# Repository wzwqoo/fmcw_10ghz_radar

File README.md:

# 10 GHz FMCW Radar Sensing Platform

A single-board **1TX / 3RX, 10 GHz FMCW radar**, its **Artix-7 range–Doppler–CFAR
backend**, and the **carrier board** that mounts the radar alongside a
global-shutter camera and an impact microphone.

The target application is a golf launch monitor: recover a ball's speed, launch
direction, spin rate and spin axis from one radar and one camera. That
application drives every architectural choice here — three non-collinear
receivers (the minimum that gives a radar-native spin axis), per-receiver
*complex* range–Doppler maps published to DDR3 (the phase the spin-axis
interferometer consumes), and a once-per-shot Ethernet offload so the heavy
post-processing runs on a host PC instead of in fabric.

```
┌─ rf_frontend/ — 10 GHz FMCW front-end ────────────────────────────────────┐
│                                                                           │
│  ADF4159 ramp PLL ──► HMC1163 10 GHz VCO ──► 4 dB branchline coupler      │
│                                                │             │            │
│                                     TX patch column    1→3 Wilkinson tree │
│                                                              │ LO         │
│  RX patch column ×3 ──► PMA3-14LN+ ──► LTC5548 ◄─────────────┘            │
│                                           │                               │
│                           ADA4940-2 IF ───┴──► ADAR7251  4 ch, 16-bit,    │
│                                                          simultaneous     │
│                                                                           │
└───────────────────────────────────────────────────────────────────────────┘
                                        │  40-pin FPC
                                        ▼
┌─ carrier_board/ — camera + radar carrier ─────────────────────────────────┐
│                                                                           │
│  radar 40-pin FPC ────────────────────────┐                               │
│  OV9281 ──MIPI──► TC358748 ──parallel─────┼──► 140-pin B2B ──► FPGA module│
│  INMP441 ──────────I2S────────────────────┘                               │
│                                                                           │
│  RTL8211F 1 GbE ◄─────────────────────────────────────────── UDP offload  │
│                                                                           │
└───────────────────────────────────────────────────────────────────────────┘
                                        │  parallel + I2S over the B2B connector
                                        ▼
┌─ fpga/ — Artix-7 backend ─────────────────────────────────────────────────┐
│                                                                           │
│  PPI bytes ──► TDM ──► BPF + Hilbert FIR ──► range FFT ×3 ──► DDR A       │
│                                                                │          │
│                        Doppler FFT ×3 ◄────────────────────────┘          │
│                              ├──► DDR B   per-RX complex RD maps          │
│                              └──► Σ|X|² ──► DDR C ──► CFAR ──► DDR D      │
│                                                                           │
│  audio + speed trigger ──► one-shot B/C/D dump ──► UDP packetizer         │
│                                                                           │
└───────────────────────────────────────────────────────────────────────────┘
                                        │
                                        ▼  host PC — trajectory, angle of arrival, spin
```

## Repository structure

| Path | Subsystem |
|---|---|
| [`rf_frontend/`](rf_frontend/) | The 10 GHz 1TX/3RX FMCW front-end: KiCad schematics and PCB on Isola 370HR, plus the ADS/Momentum EM results for every distributed structure |
| [`fpga/`](fpga/) | Artix-7 gateware: the raw-ADC → range–Doppler → CFAR pipeline, the DDR-to-host UDP offload path, MicroBlaze firmware, and the simulation stack |
| [`carrier_board/`](carrier_board/) | The carrier PCB that ties camera, radar, FPGA module, Ethernet and audio together, plus the CS-mount lens mechanics |

Each subsystem has its own README with the detail; the tables below are the map.

### `rf_frontend/` — 10 GHz FMCW front-end

A closed-loop fractional-N ramp PLL (ADF4159) drives a 10 GHz VCO (HMC1163)
across a 192 MHz sweep in 108 µs. The VCO fundamental is tapped through a 4 dB
branchline coupler and a 1→3 Wilkinson tree to supply a coherent LO to three
LNA-first receive chains (PMA3-14LN+ → LTC5548 → ADA4940-2), which land on an
ADAR7251's simultaneously-sampled channels. The antennas are series-fed patch
columns arranged in a staggered "^", stepped λ/2 between adjacent phase centres
in both array axes, so per-Doppler-bin angles never wrap.

→ [`rf_frontend/README.md`](rf_frontend/README.md)

### `fpga/` — Artix-7 digital backend

`01_adar7251_ppi_rx` → TDM mux → band-pass + Hilbert FIR → per-RX range FFT →
transposed DDR scatter (region A) → Doppler sequencer → per-RX Doppler FFT →
non-coherent integration (region C) + per-RX complex cache (region B) →
streaming cell-averaging CFAR (region D). A 128 × 256 grid, double-buffered so
software never reads a torn frame. An audio-plus-speed trigger picks the first
frame after impact that clears both gates and dumps its B/C/D regions to the
host over UDP.

→ [`fpga/README.md`](fpga/README.md)

### `carrier_board/` — camera + radar carrier

Hosts the camera FPC, the radar's 40-pin FPC, a 140-pin B2B connector to the
FPGA module, I2S audio headers, gigabit Ethernet and the power tree. Two
revisions live here: the current OV9281 design (schematics complete, layout not
yet drawn) and the earlier IMX477 design, which is where the completed layout
is.

→ [`carrier_board/README.md`](carrier_board/README.md)

## Status

| Item | State |
|---|---|
| `rf_frontend/` schematics + PCB layout | Complete; every distributed structure verified in ADS/Momentum |
| `fpga/` RTL pipeline (`01`…`08`) | Complete; unit tests and a raw-ADC-to-CFAR xsim run against the real Xilinx FFT/FIR IP |
| `fpga/` host offload (streamer, packetizer, receiver) | Complete and unit-tested |
| `fpga/firmware/audio_dsp.c` | Complete |
| `fpga/firmware/fusion_control.c` | **Work in progress** — the audio + speed trigger FSM and its frame-selection policy are still being written |
| `carrier_board/ov9281/` | **Work in progress** — schematics done, PCB layout not yet started |
| `carrier_board/imx477/` | Obsolete and not optimized — rolling-shutter sensor, hand-unfriendly USB 3.0 BGA. Kept as the revision with a finished layout |

## Toolchain

| Tool | Used for |
|---|---|
| KiCad ≥ 8 | `rf_frontend/kicad/`, `carrier_board/ov9281/`, `carrier_board/imx477/` |
| Keysight ADS + Momentum | EM verification of the antenna, coupler, splitter and LO tree |
| Vivado 2025.1 | Block design, IP generation, synthesis, the xsim end-to-end run |
| Icarus Verilog | The RTL unit tests — they need no vendor IP (`fpga/sim/run_unit_tests.sh`) |
| Python 3 (numpy, matplotlib) | Stimulus generation, CFAR golden checks, the UDP frame receiver |
| FreeCAD | `carrier_board/mechanical/CS-mount.FCStd` |

Large generated trees are deliberately out of the repository: the Vivado
project's `.runs`/`.gen`/`.cache` output, xsim build directories, and the ADS
workspace (its results are captured as images in `rf_frontend/ads/`).

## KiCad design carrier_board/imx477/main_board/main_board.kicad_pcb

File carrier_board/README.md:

# `carrier_board/` — camera + radar carrier

The board everything else plugs into: the camera, the radar, the FPGA module,
the impact microphone, Ethernet, and the power tree.

Two revisions live here. **`ov9281/` is the current design and is a work in
progress** — the schematics are complete, the PCB layout is not yet drawn.
`imx477/` is the earlier revision, superseded but kept because it is the one
with a finished layout.

---

## `ov9281/` — current revision (work in progress)

Built around the **OV9281 global-shutter sensor**. Its interfaces:

| Sheet | Interface |
|---|---|
| `extension.kicad_sch` (CAM) | Camera **FPC connector**; the sensor's MIPI CSI-2 lanes into a **TC358748XBG** bridge, which presents them as a parallel bus (PD0–PD23, PCLK, HVALID, VVALID) the FPGA captures directly. PCA9543 I²C switch and TXS0108E level shifters alongside |
| `FPGA.kicad_sch` | **140-pin board-to-board connector** (2×70, 0.5 mm) carrying the parallel camera bus, radar bus and control to the FPGA module; JTAG; and the **I²S audio headers** (BCLK / LRCLK / SD) for the impact microphone |
| `FMCW.kicad_sch` | **40-pin shielded FPC connector** to the radar front-end, with TXS0108E level translation |
| `ETH.kicad_sch` | **Gigabit Ethernet**: RTL8211F-CG PHY, HY911130A RJ45 with integrated magnetics, SN74LVC2G34 buffers |
| `power.kicad_sch` | 12 V barrel jack → TPS54302 buck and TPS74801 LDO rails |
| `footprints/` | Project-local footprint libraries |

**Layout status: not started.** `ov9281/` is schematics only — there is no
`.kicad_pcb` in this revision.

### Why Ethernet and not USB 3.0

The IMX477 revision used a CYUSB3014 for the host link. That part is a
**121-ball TFBGA**, which is not realistically hand-reflowable, and it dictated
the whole main-board stackup and layout. The OV9281 revision drops it for
gigabit Ethernet through an RTL8211F, which is a QFN and reflows by hand
without difficulty.

That change also settled the processing split. Because frames are **buffered in
DDR and then sent to a PC for processing**, rather than being consumed live on
the FPGA, the **on-FPGA blob-detection logic from the IMX477 era is obsolete**.
The FPGA's job is now capture, buffer, and offload; detection, trajectory
fitting and spin estimation all happen on the host. The radar path in
[`../fpga`](../fpga) follows the same store-and-forward pattern.

---

## `imx477/` — earlier revision (obsolete)

Built around the **IMX477**, split across a `main_board/` (FPGA module, USB 3.0
host link, power) and a separate `sensor_board/`, joined by a DF40C/DF40HC
60-pin board-to-board pair.

**The IMX477 is obsolete for this application, and this revision is not
optimized.** The sensor is rolling-shutter, which smears a fast-moving ball
across the frame in a way no amount of downstream processing recovers — a
global-shutter sensor is the requirement, and that is what the OV9281 revision
exists to satisfy. The USB 3.0 host path is the second reason it was dropped
(see above).

It is kept here because it is the only revision that carries a completed PCB
layout, and because its power tree and B2B pinout carry over.

| Path | Contents |
|---|---|
| `imx477/main_board/main_board.kicad_pro` / `.kicad_sch` / `.kicad_pcb` | KiCad project, schematics, and the finished layout |
| `imx477/main_board/USB3.kicad_sch` | CYUSB3014 USB 3.0 controller, AT24CM02 config EEPROM, VBUS switching — the path replaced by Ethernet |
| `imx477/main_board/FPGA.kicad_sch` | 2×70 B2B to the FPGA module, JTAG |
| `imx477/main_board/extension.kicad_sch` | DF40HC 60-pin B2B to the sensor board |
| `imx477/main_board/power.kicad_sch` | TLV62130 / AP3417C / MIC5504 rails |
| `imx477/sensor_board/` | The IMX477 sensor board: `sensors.kicad_sch`, `power.kicad_sch`, and its layout |
| `imx477/footprints/` | Project-local footprint libraries |

---

## `mechanical/`

`CS-mount.FCStd` — a FreeCAD CS-mount lens holder, drawn for the IMX477 sensor
board. `lens_spec.png` records the optics it was sized around: a 4 mm lens
giving roughly 90° horizontal field of view, paired with 940 nm IR flood
illumination so exposures stay short enough for 200 fps and above.

---

## Opening the boards

```
kicad carrier_board/ov9281/hardware.kicad_pro           # KiCad 8 or newer
kicad carrier_board/imx477/main_board/main_board.kicad_pro
kicad carrier_board/imx477/sensor_board/sensor_board.kicad_pro
```

The render above was produced with `kicad-cli pcb render`.

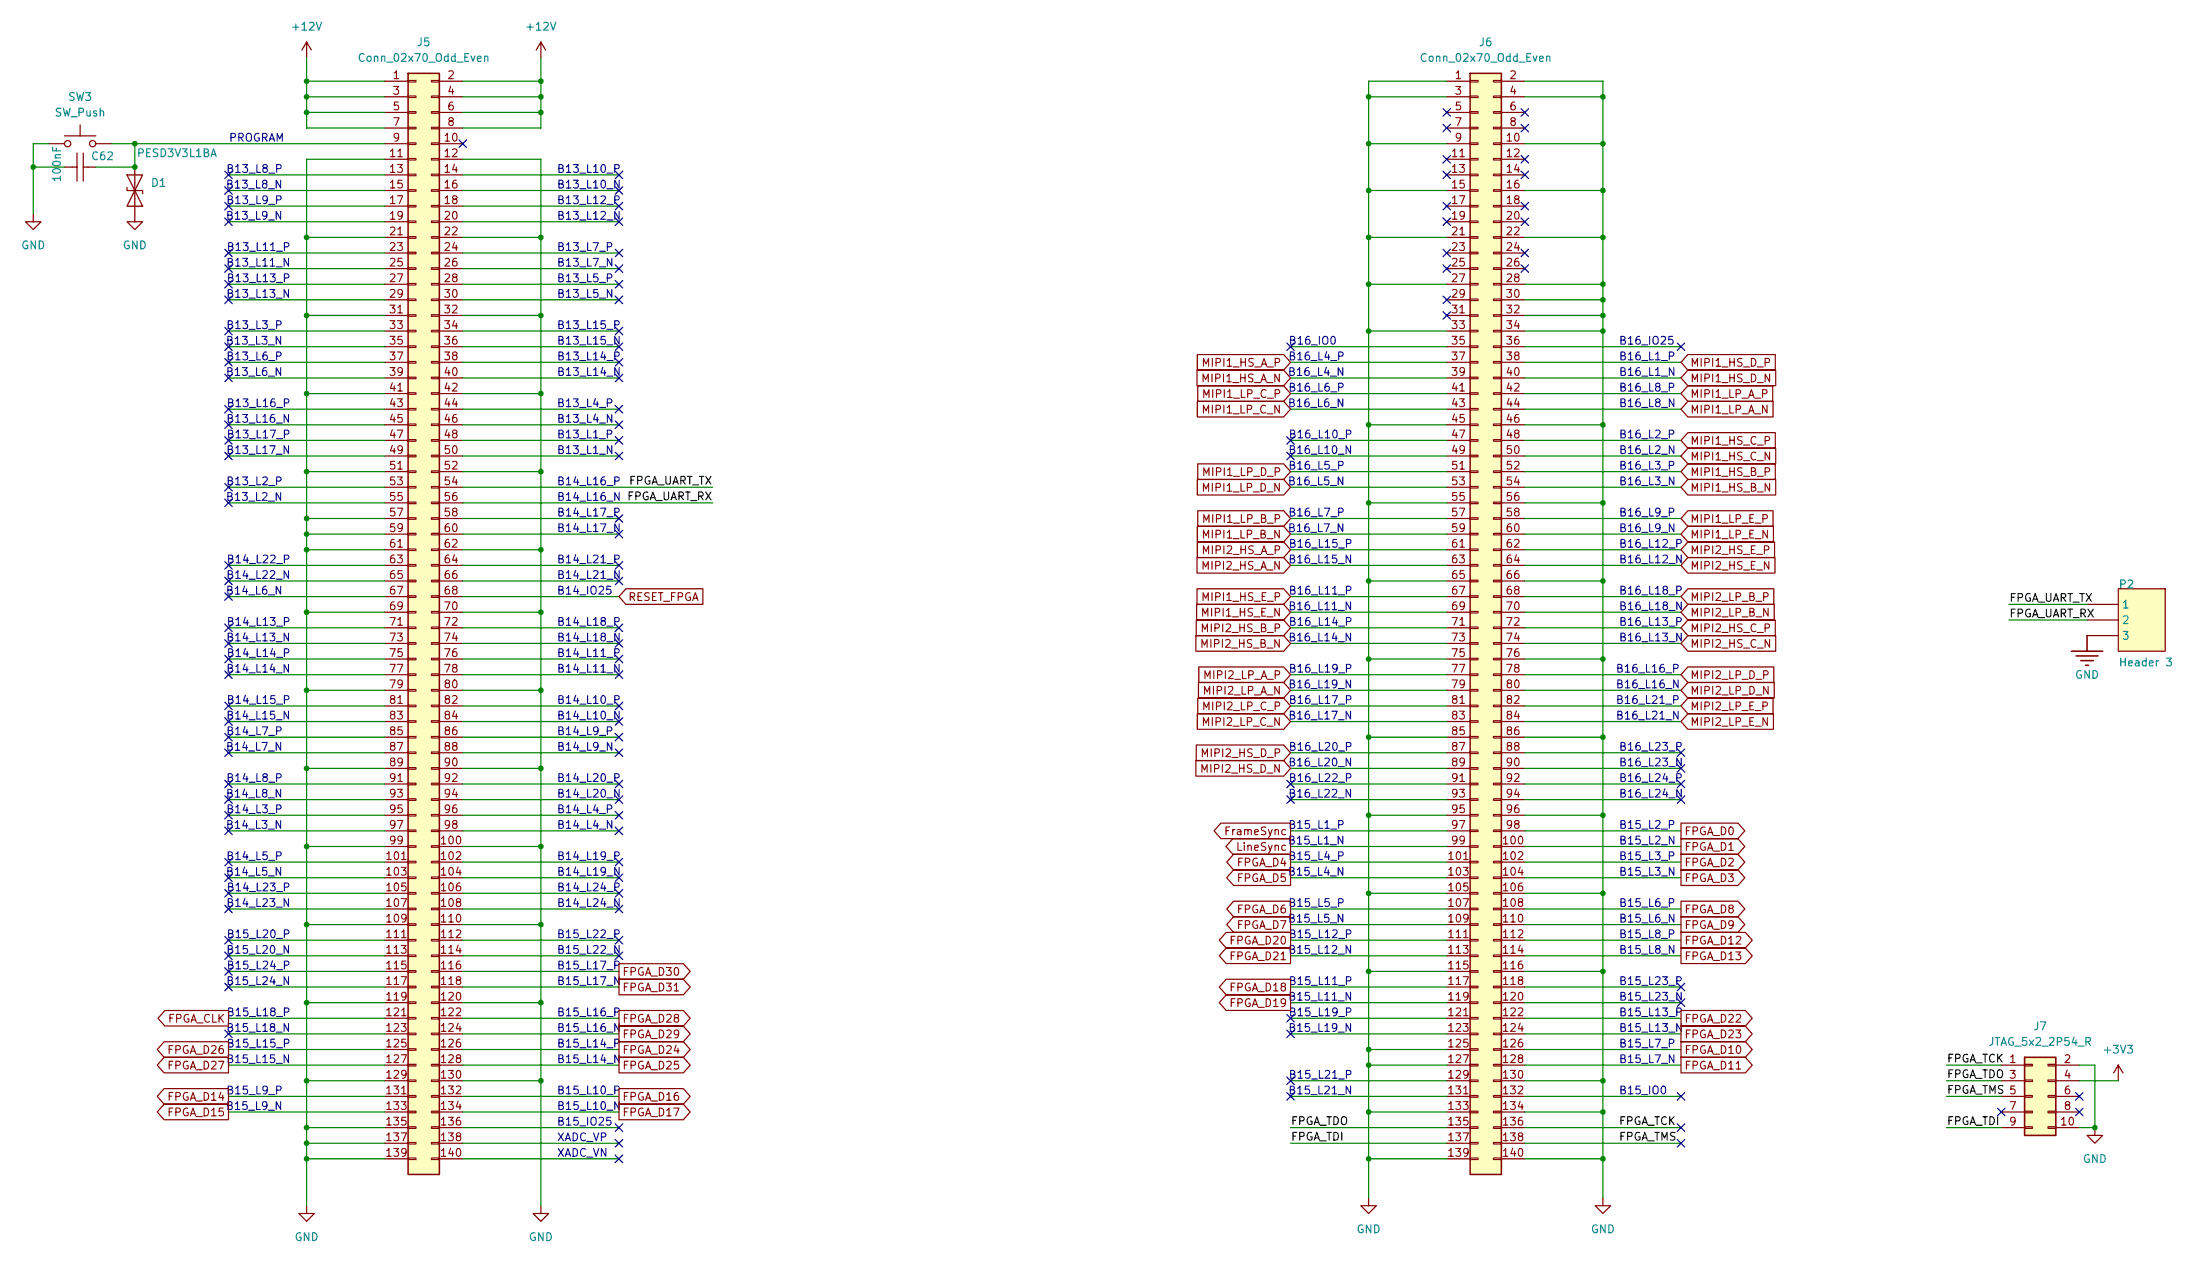
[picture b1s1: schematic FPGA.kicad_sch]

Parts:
C62: 100nF; C_0603_1608Metric; TOLERANCE ±10%; RATINGS 16V; X7R; MANUFACTURER PART NUMBE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 CC0402KRX7R7BB103
D1: PESD3V3L1BA; D_SOD-323
J5, J6: Conn_02x70_Odd_Even; CONN-SMD_140P-P0.50_B2BM-2X70-0P5_BZOOC
J7: JTAG_5x2_2P54_R; PinHeader_2x05_P2.54mm_Horizontal
P2: Header 3; PinHeader_1x03_P2.54mm_Vertical
SW3: SW_Push; SW_Push_1P1T_NO_CK_KMR2; Part# KMR242NGLFS; LCSC Part # C2804669

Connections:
+3V3: J7.4; also elsewhere on the board
+12V: J5.1, J5.2, J5.3, J5.4, J5.5, J5.6, J5.7, J5.8; also elsewhere on the board
/FPGA/FPGA_TCK: J6.136, J7.1
/FPGA/FPGA_TDI: J6.137, J7.9
/FPGA/FPGA_TDO: J6.135, J7.3
/FPGA/FPGA_TMS: J6.138, J7.5
/FPGA/FPGA_UART_RX: J5.56, P2.2
/FPGA/FPGA_UART_TX: J5.54, P2.1
FPGA_CLK: J5.121; also elsewhere on the board
FPGA_D0: J6.98; also elsewhere on the board
FPGA_D1: J6.100; also elsewhere on the board
FPGA_D2: J6.102; also elsewhere on the board
FPGA_D3: J6.104; also elsewhere on the board
FPGA_D4: J6.101; also elsewhere on the board
FPGA_D5: J6.103; also elsewhere on the board
FPGA_D6: J6.107; also elsewhere on the board
FPGA_D7: J6.109; also elsewhere on the board
FPGA_D8: J6.108; also elsewhere on the board
FPGA_D9: J6.110; also elsewhere on the board
FPGA_D10: J6.126; also elsewhere on the board
FPGA_D11: J6.128; also elsewhere on the board
FPGA_D12: J6.112; also elsewhere on the board
FPGA_D13: J6.114; also elsewhere on the board
FPGA_D14: J5.131; also elsewhere on the board
FPGA_D15: J5.133; also elsewhere on the board
FPGA_D16: J5.132; also elsewhere on the board
FPGA_D17: J5.134; also elsewhere on the board
FPGA_D18: J6.117; also elsewhere on the board
FPGA_D19: J6.119; also elsewhere on the board
FPGA_D20: J6.111; also elsewhere on the board
FPGA_D21: J6.113; also elsewhere on the board
FPGA_D22: J6.122; also elsewhere on the board
FPGA_D23: J6.124; also elsewhere on the board
FPGA_D24: J5.126; also elsewhere on the board
FPGA_D25: J5.128; also elsewhere on the board
FPGA_D26: J5.125; also elsewhere on the board
FPGA_D27: J5.127; also elsewhere on the board
FPGA_D28: J5.122; also elsewhere on the board
FPGA_D29: J5.124; also elsewhere on the board
FPGA_D30: J5.116; also elsewhere on the board
FPGA_D31: J5.118; also elsewhere on the board
FrameSync: J6.97; also elsewhere on the board
GND: C62.2, D1.1 (A1), J5.11, J5.12, J5.21, J5.22, J5.31, J5.32, J5.41, J5.42, J5.51, J5.52, J5.57, J5.59, J5.61, J5.62, J5.69, J5.70, J5.79, J5.80, J5.89, J5.90, J5.99, J5.100, J5.109, J5.110, J5.119, J5.120, J5.129, J5.130, J5.135, J5.137, J5.139, J6.1, J6.2, J6.3, J6.4, J6.9, J6.10, J6.15, J6.16, J6.21, J6.22, J6.27, J6.28, J6.30, J6.32, J6.33, J6.34, J6.45, J6.46, J6.55, J6.56, J6.65, J6.66, J6.75, J6.76, J6.85, J6.86, J6.95, J6.96, J6.105, J6.106, J6.115, J6.116, J6.125, J6.127, J6.130, J6.133, J6.134, J6.139, J6.140, J7.2, J7.10, P2.3, SW3.1; also elsewhere on the board
LineSync: J6.99; also elsewhere on the board
MIPI1_HS_A_N: J6.39; also elsewhere on the board
MIPI1_HS_A_P: J6.37; also elsewhere on the board
MIPI1_HS_B_N: J6.54; also elsewhere on the board
MIPI1_HS_B_P: J6.52; also elsewhere on the board
MIPI1_HS_C_N: J6.50; also elsewhere on the board
MIPI1_HS_C_P: J6.48; also elsewhere on the board
MIPI1_HS_D_N: J6.40; also elsewhere on the board
MIPI1_HS_D_P: J6.38; also elsewhere on the board
MIPI1_HS_E_N: J6.69; also elsewhere on the board
MIPI1_HS_E_P: J6.67; also elsewhere on the board
MIPI1_LP_A_N: J6.44; also elsewhere on the board
MIPI1_LP_A_P: J6.42; also elsewhere on the board
MIPI1_LP_B_N: J6.59; also elsewhere on the board
MIPI1_LP_B_P: J6.57; also elsewhere on the board
MIPI1_LP_C_N: J6.43; also elsewhere on the board
MIPI1_LP_C_P: J6.41; also elsewhere on the board
MIPI1_LP_D_N: J6.53; also elsewhere on the board
MIPI1_LP_D_P: J6.51; also elsewhere on the board
MIPI1_LP_E_N: J6.60; also elsewhere on the board
MIPI1_LP_E_P: J6.58; also elsewhere on the board
MIPI2_HS_A_N: J6.63; also elsewhere on the board
MIPI2_HS_A_P: J6.61; also elsewhere on the board
MIPI2_HS_B_N: J6.73; also elsewhere on the board
MIPI2_HS_B_P: J6.71; also elsewhere on the board
MIPI2_HS_C_N: J6.74; also elsewhere on the board
MIPI2_HS_C_P: J6.72; also elsewhere on the board
MIPI2_HS_D_N: J6.89; also elsewhere on the board
MIPI2_HS_D_P: J6.87; also elsewhere on the board
MIPI2_HS_E_N: J6.64; also elsewhere on the board
MIPI2_HS_E_P: J6.62; also elsewhere on the board
MIPI2_LP_A_N: J6.79; also elsewhere on the board
MIPI2_LP_A_P: J6.77; also elsewhere on the board
MIPI2_LP_B_N: J6.70; also elsewhere on the board
MIPI2_LP_B_P: J6.68; also elsewhere on the board
MIPI2_LP_C_N: J6.83; also elsewhere on the board
MIPI2_LP_C_P: J6.81; also elsewhere on the board
MIPI2_LP_D_N: J6.80; also elsewhere on the board
MIPI2_LP_D_P: J6.78; also elsewhere on the board
MIPI2_LP_E_N: J6.84; also elsewhere on the board
MIPI2_LP_E_P: J6.82; also elsewhere on the board
unnamed: C62.1, D1.2 (A2), J5.9, SW3.2
RESET_FPGA: J5.68; also elsewhere on the board

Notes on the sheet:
B16_L14_N
B14_L24_P
B14_L15_P
B16_L1_P
B14_L22_N
B15_L5_P
B16_L3_P
B16_L13_N
B15_L17_N
B13_L6_P
B16_L21_N
B14_L14_P
B15_L1_N
B13_L2_P
B15_L24_P
B15_L15_P
B14_IO25
B16_L20_P
B14_L18_P
B13_L13_N
B16_L24_N
B15_L7_P
B13_L16_N
B13_L13_P
B15_L11_N
B15_L21_N
B15_L22_P
B15_L20_P
B13_L1_P
B14_L9_P
B13_L4_P
B13_L14_N
B15_L14_P
B15_L24_N
B16_L11_P
B14_L3_P
B15_L8_N
B13_L8_N
B13_L14_P
B15_L23_P

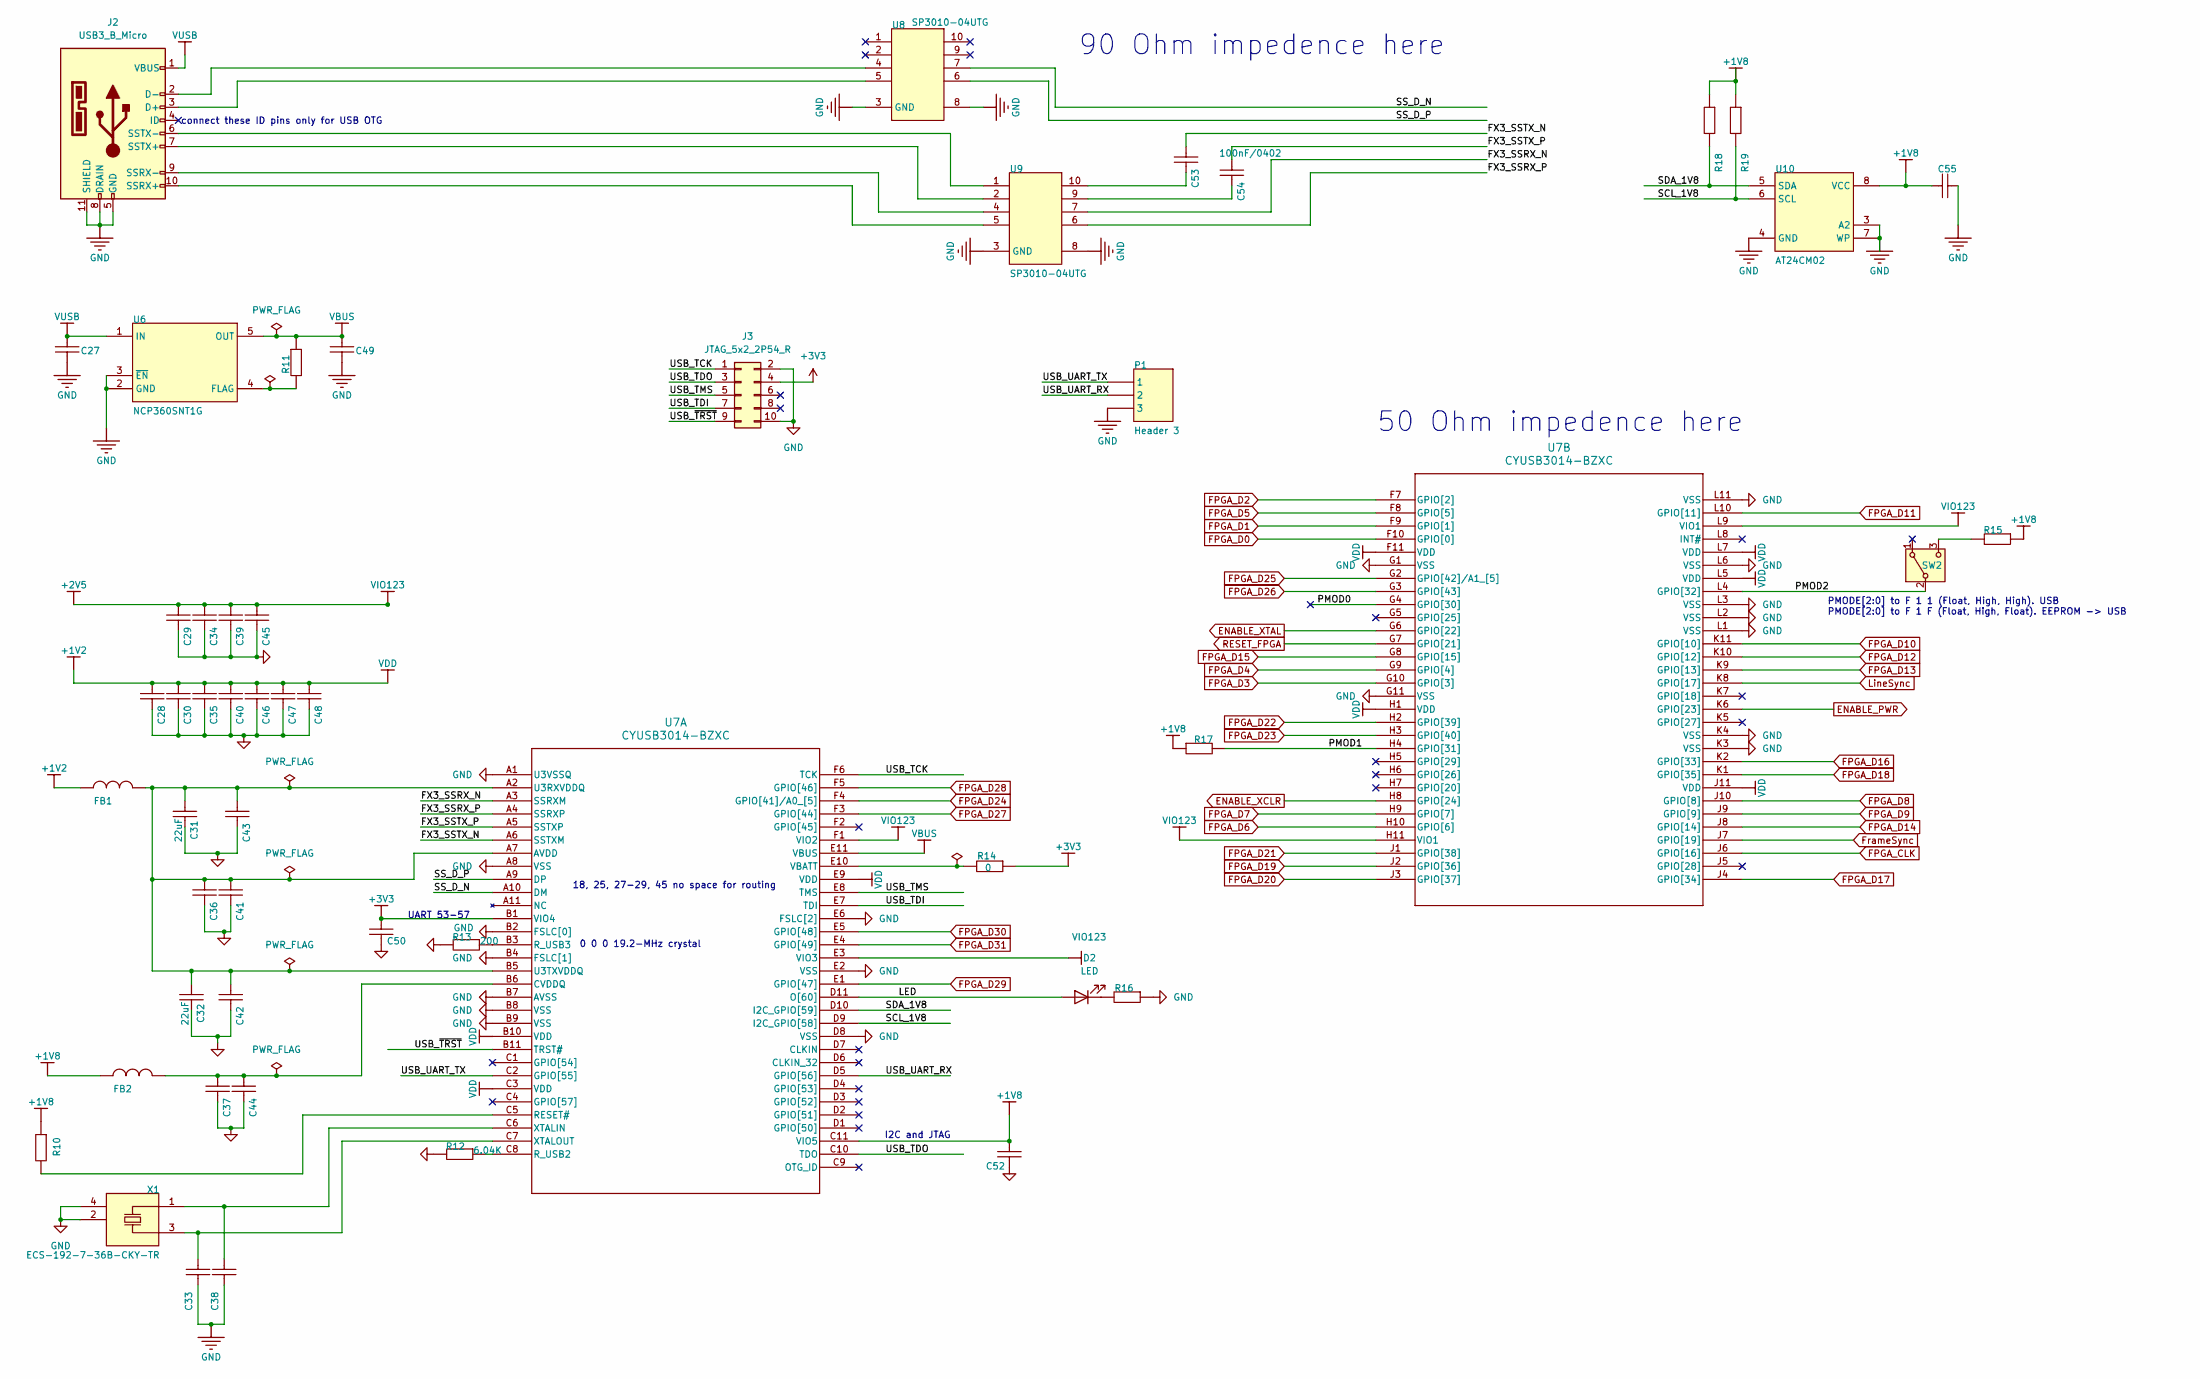
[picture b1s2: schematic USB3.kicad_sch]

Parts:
C27, C49: 10uF; C_0603_1608Metric; TOLERANCE ±20%; RATINGS 50V; X5R; MANUFACTURER PART NUMBE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 UMK325BJ106MM-T
C28, C29, C30, C33, C34, C35, C36, C37, C38, C39, C40, C42, C43, C44, C45, C46, C47, C48, C50, C52, C55: 100nF; C_0603_1608Metric; TOLERANCE ±10%; RATINGS 16V; X7R; MANUFACTURER PART NUMBE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 CC0402KRX7R7BB103
C31, C32: 22uF; C_0603_1608Metric; RATINGS 50V; NP0; MANUFACTURER PART NUMBE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 06035A561JAT2A
C41: 2.2uF; C_0603_1608Metric; TOLERANCE ±10%; RATINGS 16V; X7R; MANUFACTURER PART NUMBE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 CC0402KRX7R7BB103
C53, C54: 100nF/0402; C_0402_1005Metric; TOLERANCE ±10%; RATINGS 16V; X7R; MANUFACTURER PART NUMBE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 CC0402KRX7R7BB103
D2: LED; LED_0603_1608Metric
FB1, FB2: 100Ω at 100 MHz; L_0805_2012Metric; Part# MPZ2012S101ATD25; LCSC Part # C307776
J2: USB3_B_Micro; USB3_Micro-B_Connfly_DS1104-01
J3: JTAG_5x2_2P54_R; PinHeader_2x05_P2.54mm_Horizontal
P1: Header 3; PinHeader_1x03_P2.54mm_Vertical
R10, R11, R15, R16, R17, R18, R19: 3.3K; R_0603_1608Metric; RATINGS 1/16 W; TOLERANCE ±5%; MANUFACTURER PART NUMBE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 RC0402JR-073K3L
R12: 6.04K; R_0603_1608Metric; RATINGS 1/16 W; TOLERANCE ±5%; MANUFACTURER PART NUMBE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 RC0402JR-073K3L
R13: 200; R_0603_1608Metric; RATINGS 1/16 W; TOLERANCE ±5%; MANUFACTURER PART NUMBE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 RC0402JR-073K3L
R14: 0; R_0603_1608Metric; RATINGS 1/16 W; TOLERANCE ±5%; MANUFACTURER PART NUMBE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 RC0402JR-073K3L
SW2: SW_SPDT; SW_SPDT_CK_JS102011SAQN; Part# JS102011SAQN; LCSC Part # C221660
U6: NCP360SNT1G; TSOP5_3X1P5_ONS; Part# NCP360SNT1G; LCSC Part # C603707
U7: CYUSB3014-BZXC; PG-TFBGA-121-800_INF
U8, U9: SP3010-04UTG; Diodes_UDFN-10_1.0x2.5mm_P0.5mm; Part# SP3010-04UTG; LCSC Part # C126837
U10: AT24CM02; SOIC-8-1EP_3.9x4.9mm_P1.27mm_EP2.29x3mm; Part# AT24CM02-SSHM-T; LCSC Part # C779670
X1: ECS-192-7-36B-CKY-TR; Oscillator_SMD_ECS_2520MV-xxx-xx-4Pin_2.5x2.0mm; Part# ECS ECS-192-7-36B-CKY-TR; LCSC Part # C2450510

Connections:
+1V2: C28.2, C30.2, C35.2, C40.2, C46.2, C47.2, C48.2, FB1.1, U7.B10 (VDD), U7.C3 (VDD), U7.E9 (VDD), U7.F11 (VDD), U7.H1 (VDD), U7.J11 (VDD), U7.L5 (VDD), U7.L7 (VDD); also elsewhere on the board
+1V8: C52.2, C55.2, FB2.1, R10.1, R15.2, R17.2, R18.1, R19.1, U7.C11 (VIO5), U10.8 (VCC); also elsewhere on the board
+2V5: C29.2, C34.2, C39.2, C45.2, U7.E3 (VIO3), U7.F1 (VIO2), U7.H11 (VIO1), U7.L9 (VIO1); also elsewhere on the board
+3V3: C50.2, J3.4, R14.2, U7.B1 (VIO4); also elsewhere on the board
/USB3/FX3_SSRX_N: U7.A3 (SSRXM), U9.7
/USB3/FX3_SSRX_P: U7.A4 (SSRXP), U9.6
/USB3/FX3_SSTX_N: C53.2, U7.A6 (SSTXM)
/USB3/FX3_SSTX_P: C54.2, U7.A5 (SSTXP)
/USB3/LED: D2.2 (A), U7.D11 (O[60])
/USB3/PMOD0: U7.G4 (GPIO[30])
/USB3/PMOD1: R17.1, U7.H4 (GPIO[31])
/USB3/PMOD2: SW2.2 (B), U7.L4 (GPIO[32])
/USB3/SCL_1V8: R19.2, U7.D9 (I2C_GPIO[58]), U10.6 (SCL)
/USB3/SDA_1V8: R18.2, U7.D10 (I2C_GPIO[59]), U10.5 (SDA)
/USB3/SS_D_N: U7.A10 (DM), U8.7
/USB3/SS_D_P: U7.A9 (DP), U8.6
/USB3/USB_TCK: J3.1, U7.F6 (TCK)
/USB3/USB_TDI: J3.7, U7.E7 (TDI)
/USB3/USB_TDO: J3.3, U7.C10 (TDO)
/USB3/USB_TMS: J3.5, U7.E8 (TMS)
/USB3/USB_UART_RX: P1.2, U7.D5 (GPIO[56])
/USB3/USB_UART_TX: P1.1, U7.C2 (GPIO[55])
/USB3/USB_~TRST: J3.9, U7.B11 (TRST#)
ENABLE_PWR: U7.K6 (GPIO[23]); also elsewhere on the board
ENABLE_XCLR: U7.H8 (GPIO[24]); also elsewhere on the board
ENABLE_XTAL: U7.G6 (GPIO[22]); also elsewhere on the board
FPGA_CLK: U7.J6 (GPIO[16]); also elsewhere on the board
FPGA_D0: U7.F10 (GPIO[0]); also elsewhere on the board
FPGA_D1: U7.F9 (GPIO[1]); also elsewhere on the board
FPGA_D2: U7.F7 (GPIO[2]); also elsewhere on the board
FPGA_D3: U7.G10 (GPIO[3]); also elsewhere on the board
FPGA_D4: U7.G9 (GPIO[4]); also elsewhere on the board
FPGA_D5: U7.F8 (GPIO[5]); also elsewhere on the board
FPGA_D6: U7.H10 (GPIO[6]); also elsewhere on the board
FPGA_D7: U7.H9 (GPIO[7]); also elsewhere on the board
FPGA_D8: U7.J10 (GPIO[8]); also elsewhere on the board
FPGA_D9: U7.J9 (GPIO[9]); also elsewhere on the board
FPGA_D10: U7.K11 (GPIO[10]); also elsewhere on the board
FPGA_D11: U7.L10 (GPIO[11]); also elsewhere on the board
FPGA_D12: U7.K10 (GPIO[12]); also elsewhere on the board
FPGA_D13: U7.K9 (GPIO[13]); also elsewhere on the board
FPGA_D14: U7.J8 (GPIO[14]); also elsewhere on the board
FPGA_D15: U7.G8 (GPIO[15]); also elsewhere on the board
FPGA_D16: U7.K2 (GPIO[33]); also elsewhere on the board
FPGA_D17: U7.J4 (GPIO[34]); also elsewhere on the board
FPGA_D18: U7.K1 (GPIO[35]); also elsewhere on the board
FPGA_D19: U7.J2 (GPIO[36]); also elsewhere on the board
FPGA_D20: U7.J3 (GPIO[37]); also elsewhere on the board
FPGA_D21: U7.J1 (GPIO[38]); also elsewhere on the board
FPGA_D22: U7.H2 (GPIO[39]); also elsewhere on the board
FPGA_D23: U7.H3 (GPIO[40]); also elsewhere on the board
FPGA_D24: U7.F4 (GPIO[41]/A0_[5]); also elsewhere on the board
FPGA_D25: U7.G2 (GPIO[42]/A1_[5]); also elsewhere on the board
FPGA_D26: U7.G3 (GPIO[43]); also elsewhere on the board
FPGA_D27: U7.F3 (GPIO[44]); also elsewhere on the board
FPGA_D28: U7.F5 (GPIO[46]); also elsewhere on the board
FPGA_D29: U7.E1 (GPIO[47]); also elsewhere on the board
FPGA_D30: U7.E5 (GPIO[48]); also elsewhere on the board
FPGA_D31: U7.E4 (GPIO[49]); also elsewhere on the board
FrameSync: U7.J7 (GPIO[19]); also elsewhere on the board
GND: C27.2, C28.1, C29.1, C30.1, C31.2, C32.2, C33.2, C34.1, C35.1, C36.1, C37.1, C38.2, C39.1, C40.1, C41.1, C42.1, C43.1, C44.1, C45.1, C46.1, C47.1, C48.1, C49.2, C50.1, C52.1, C55.1, J2.5 (GND), J2.8 (DRAIN), J2.11 (SHIELD), J3.2, J3.10, P1.3, R12.1, R13.1, R16.2, U6.2 (GND), U6.3 (~EN), U7.A1 (U3VSSQ), U7.A8 (VSS), U7.B2 (FSLC[0]), U7.B4 (FSLC[1]), U7.B7 (AVSS), U7.B8 (VSS), U7.B9 (VSS), U7.D8 (VSS), U7.E2 (VSS), U7.E6 (FSLC[2]), U7.G1 (VSS), U7.G11 (VSS), U7.K3 (VSS), U7.K4 (VSS), U7.L1 (VSS), U7.L2 (VSS), U7.L3 (VSS), U7.L6 (VSS), U7.L11 (VSS), U8.3 (GND), U8.8 (GND), U9.3 (GND), U9.8 (GND), U10.3 (A2), U10.4 (GND), U10.7 (WP), X1.2 (NC), X1.4 (NC); also elsewhere on the board
LineSync: U7.K8 (GPIO[17]); also elsewhere on the board
unnamed: C53.1, U9.10
unnamed: C54.1, U9.9
unnamed: D2.1 (K), R16.1
unnamed: J2.3 (D+), U8.5
unnamed: J2.2 (D-), U8.4
unnamed: J2.10 (SSRX+), U9.5
unnamed: J2.9 (SSRX-), U9.4
unnamed: J2.7 (SSTX+), U9.2
unnamed: J2.6 (SSTX-), U9.1
unnamed: R15.1, SW2.3 (C)
unnamed: R11.1, U6.4 (FLAG)
unnamed: C31.1, C32.1, C36.2, C41.2, C42.2, C43.2, FB1.2, U7.A2 (U3RXVDDQ), U7.A7 (AVDD), U7.B5 (U3TXVDDQ)
unnamed: C37.2, C44.2, FB2.2, U7.B6 (CVDDQ)
unnamed: R10.2, U7.C5 (RESET#)
unnamed: R12.2, U7.C8 (R_USB2)
unnamed: R13.2, U7.B3 (R_USB3)
unnamed: R14.1, U7.E10 (VBATT)
unnamed: C38.1, U7.C6 (XTALIN), X1.1 (X1)
unnamed: C33.1, U7.C7 (XTALOUT), X1.3 (X2)
RESET_FPGA: U7.G7 (GPIO[21]); also elsewhere on the board
VBUS: C49.1, R11.2, U6.5 (OUT), U7.E11 (VBUS)
VUSB: C27.1, J2.1 (VBUS), U6.1 (IN)

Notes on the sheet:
0 0 0 19.2-MHz crystal
UART 53-57
connect these ID pins only for USB OTG
I2C and JTAG
18, 25, 27-29, 45 no space for routing
90 Ohm impedence here
PMODE[2:0] to F 1 1 (Float, High, High). USB PMODE[2:0] to F 1 F (Float, High, Float). EEPROM -> USB
50 Ohm impedence here

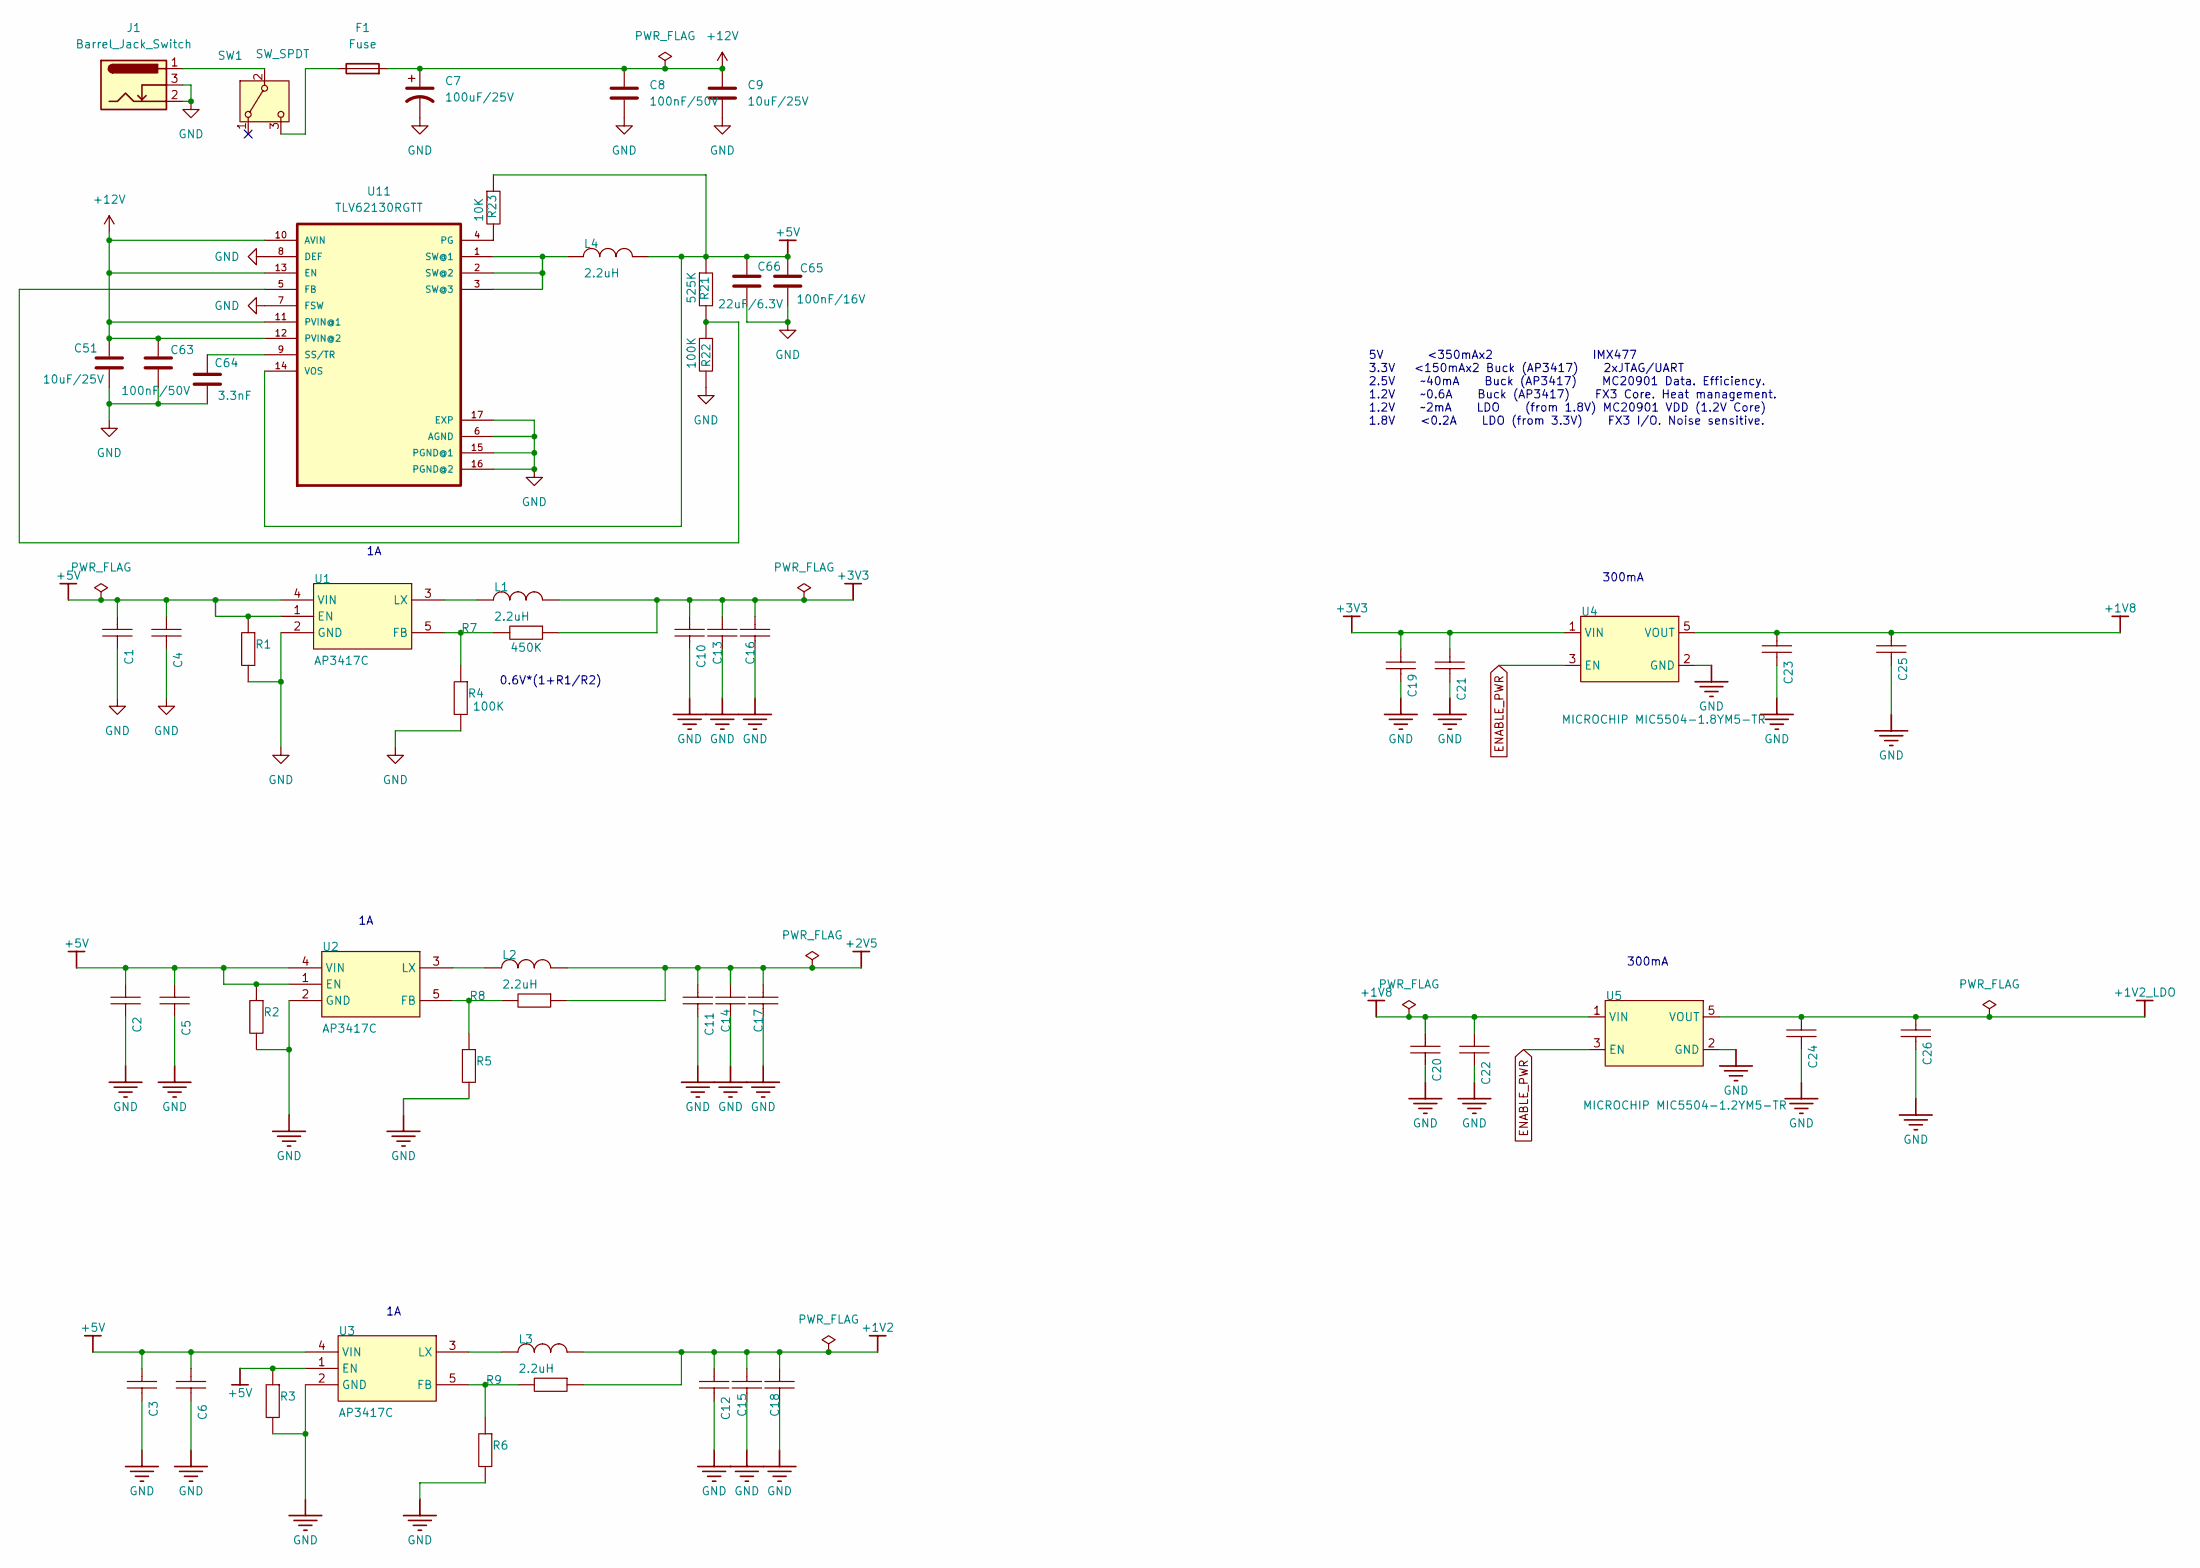
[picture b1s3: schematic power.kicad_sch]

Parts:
C1, C2, C3, C19, C20, C25, C26: 10uF; C_0603_1608Metric; RATINGS 50V; NP0; MANUFACTURER PART NUMBE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 06035A561JAT2A
C4, C5, C6, C10, C11, C12, C21, C22, C23, C24: 100nF; C_0603_1608Metric; TOLERANCE ±10%; RATINGS 16V; X7R; MANUFACTURER PART NUMBE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 CC0402KRX7R7BB103
C7: 100uF/25V; CP_Elec_6.3x5.7
C8, C63: 100nF/50V; C_0603_1608Metric
C9, C51: 10uF/25V; C_0603_1608Metric
C13, C14, C15, C16, C17, C18: 10uF; C_0603_1608Metric; TOLERANCE ±10%; RATINGS 16V; X5R; MANUFACTURER PART NUMBE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 EMK212BJ475KG-T
C64: 3.3nF; C_0603_1608Metric
C65: 100nF/16V; C_0603_1608Metric
C66: 22uF/6.3V; C_0603_1608Metric
F1: Fuse; Fuse_1812_4532Metric; Part# SMD1812P200TF16; LCSC Part # C20812
J1: Barrel_Jack_Switch; BarrelJack_CLIFF_FC681465S_SMT_Horizontal; Part# TBD
L1, L2, L3, L4: 2.2uH; L_Taiyo-Yuden_MD-4040; Part# CMLO0420H2R2MTT; LCSC Part # C438930
R1, R2, R3, R23: 10K; R_0603_1608Metric; RATINGS 1/16 W; TOLERANCE ±5%; MANUFACTURER PART NUMBE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 RC0402JR-073K3L
R4, R5, R6, R9, R22: 100K; R_0603_1608Metric; RATINGS 1/16 W; TOLERANCE ±5%; MANUFACTURER PART NUMBE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 RC0402JR-073K3L
R7: 450K; R_0603_1608Metric; RATINGS 1/16 W; TOLERANCE ±5%; MANUFACTURER PART NUMBE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 RC0402JR-073K3L
R8: 320K; R_0603_1608Metric; RATINGS 1/16 W; TOLERANCE ±5%; MANUFACTURER PART NUMBE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 RC0402JR-073K3L
R21: 525K; R_0603_1608Metric; RATINGS 1/16 W; TOLERANCE ±5%; MANUFACTURER PART NUMBE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 RC0402JR-073K3L
SW1: SW_SPDT; SW_SPDT_CK_JS102011SAQN; Part# JS102011SAQN; LCSC Part # C221660
U1, U2, U3: AP3417C; SOT-23-5; Part# AP3417CKTR-G1; LCSC Part # C500759
U4: MICROCHIP MIC5504-1.8YM5-TR; SOT-23-5; Part# MIC5504-1.8YM5-TR; LCSC Part # C626116
U5: MICROCHIP MIC5504-1.2YM5-TR; SOT-23-5; Part# MIC5504-1.8YM5-TR; LCSC Part # C626116
U11: TLV62130RGTT; VQFN-16-1EP_3x3mm_P0.5mm_EP1.6x1.6mm; DigiKey_Part_Number 296-32407-1-ND

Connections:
+1V2: C12.2, C15.1, C18.1, L3.2, R9.2; also elsewhere on the board
+1V2_LDO: C24.2, C26.1, U5.5 (VOUT); also elsewhere on the board
+1V8: C20.1, C22.2, C23.2, C25.1, U4.5 (VOUT), U5.1 (VIN); also elsewhere on the board
+2V5: C11.2, C14.1, C17.1, L2.2, R8.2; also elsewhere on the board
+3V3: C10.2, C13.1, C16.1, C19.1, C21.2, L1.2, R7.2, U4.1 (VIN); also elsewhere on the board
+5V: C1.1, C2.1, C3.1, C4.2, C5.2, C6.2, C65.1, C66.1, L4.2, R1.2, R2.2, R3.2, R21.2, R23.2, U1.1 (EN), U1.4 (VIN), U2.1 (EN), U2.4 (VIN), U3.1 (EN), U3.4 (VIN), U11.14 (VOS); also elsewhere on the board
+12V: C7.1, C8.1, C9.1, C51.1, C63.1, F1.2, U11.10 (AVIN), U11.11 (PVIN@1), U11.12 (PVIN@2), U11.13 (EN); also elsewhere on the board
ENABLE_PWR: U4.3 (EN), U5.3 (EN); also elsewhere on the board
GND: C1.2, C2.2, C3.2, C4.1, C5.1, C6.1, C7.2, C8.2, C9.2, C10.1, C11.1, C12.1, C13.2, C14.2, C15.2, C16.2, C17.2, C18.2, C19.2, C20.2, C21.1, C22.1, C23.1, C24.1, C25.2, C26.2, C51.2, C63.2, C64.2, C65.2, C66.2, J1.2, J1.3, R1.1, R2.1, R3.1, R4.1, R5.1, R6.1, R22.1, U1.2 (GND), U2.2 (GND), U3.2 (GND), U4.2 (GND), U5.2 (GND), U11.6 (AGND), U11.7 (FSW), U11.8 (DEF), U11.15 (PGND@1), U11.16 (PGND@2), U11.17 (EXP); also elsewhere on the board
unnamed: J1.1, SW1.2 (B)
unnamed: F1.1, SW1.3 (C)
unnamed: R4.2, R7.1, U1.5 (FB)
unnamed: L1.1, U1.3 (LX)
unnamed: R5.2, R8.1, U2.5 (FB)
unnamed: L2.1, U2.3 (LX)
unnamed: R6.2, R9.1, U3.5 (FB)
unnamed: L3.1, U3.3 (LX)
unnamed: R21.1, R22.2, U11.5 (FB)
unnamed: R23.1, U11.4 (PG)
unnamed: C64.1, U11.9 (SS/TR)
unnamed: L4.1, U11.1 (SW@1), U11.2 (SW@2), U11.3 (SW@3)

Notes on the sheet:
300mA
0.6V*(1+R1/R2)
5V <350mAx2 IMX477 3.3V <150mAx2 Buck (AP3417) 2xJTAG/UART 2.5V ~40mA Buck (AP3417) MC20901 Data. Efficiency. 1.2V ~0.6A Buck (AP3417) FX3 Core. Heat management. 1.2V ~2mA LDO (from 1.8V) MC20901 VDD (1.2V Core) 1.8V <0.2A LDO (from 3.3V) FX3 I/O. Noise sensitive.
